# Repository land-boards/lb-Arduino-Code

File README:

These are my arduino files. Some of these files (particularly libraries) were created by others. 

Many of them were created by me based on the work of others.

Use at your own risk. If you brick your part or it melt to a puddle, it's on you not me.

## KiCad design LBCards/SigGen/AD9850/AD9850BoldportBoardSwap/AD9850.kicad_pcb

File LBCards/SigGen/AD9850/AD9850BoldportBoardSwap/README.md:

### AD9850 Signal Generator Boldport Board Swap Version

This is the KiCAD files and Gerber files for the Boldport Board Swap.  It is a driver board for an AD9850 module. It uses an  ATMega328p as the controll chip and includes a display as well as two rotary encoders to support a UI.

It is based on the project:

http://www.vwlowen.co.uk/arduino/AD9850-waveform-generator/AD9850-waveform-generator.htm

Which in turn is based on AD9851 code from Andrew Smallbone - modified for AD9850 http://www.rocketnumbernine.com/2011/10/25/programming-the-ad9851-dds-synthesizer

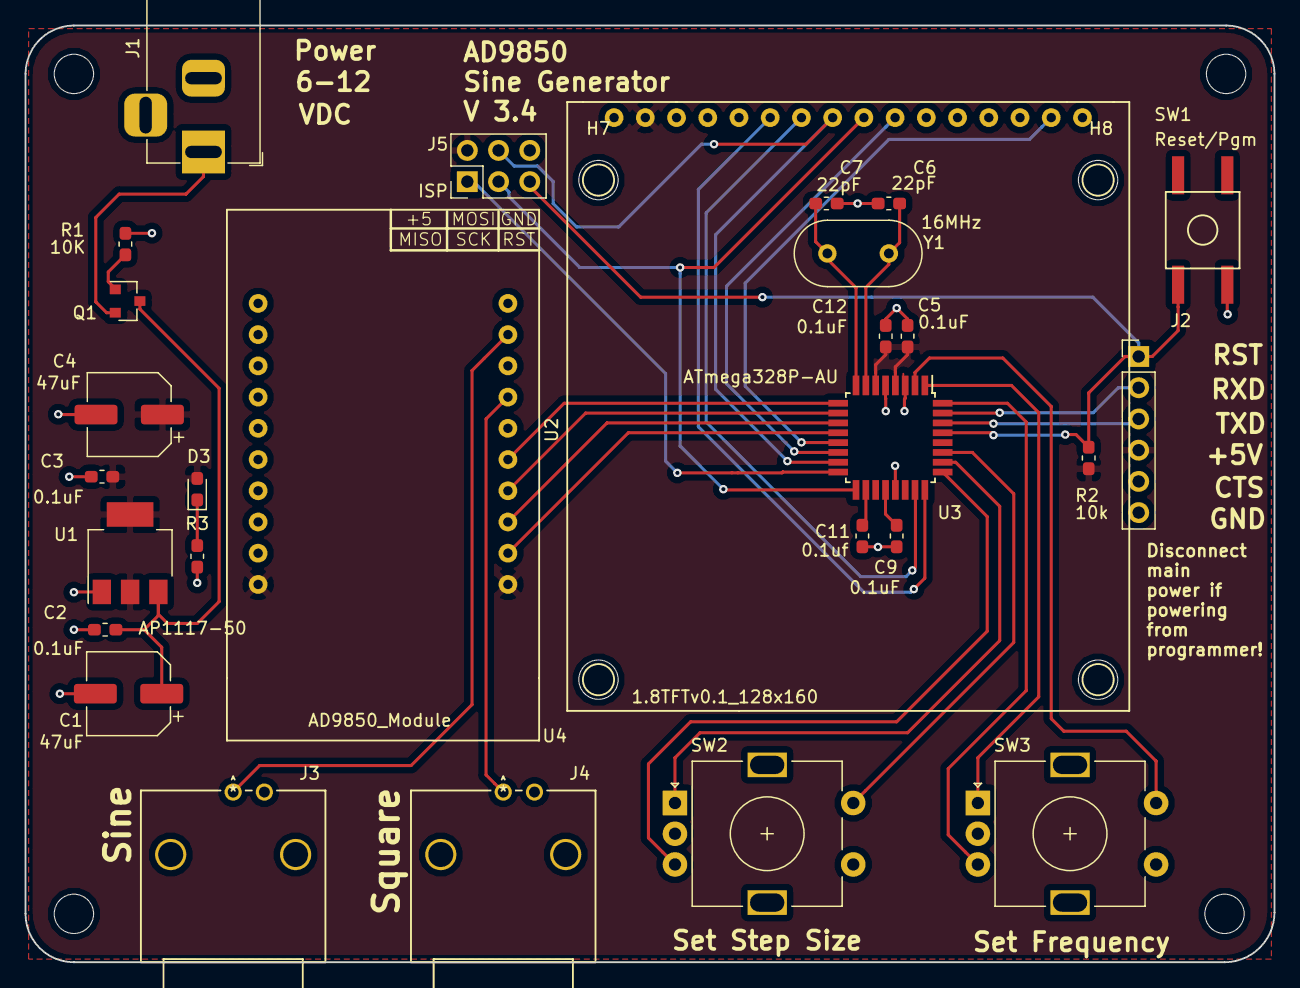
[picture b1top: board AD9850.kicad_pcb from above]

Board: 2 copper layers, 101.6 x 76.2 mm, 36 parts (0 on the bottom side), 32 nets.

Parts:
C1, C4: 47uF; CP_Elec_6.3x7.7
C2, C3, C5, C9, C12: 0.1uF; C_0603_1608Metric_Pad1.05x0.95mm_HandSolder
C6, C7: 22pF; C_0603_1608Metric_Pad1.05x0.95mm_HandSolder
C11: 0.1uf; C_0603_1608Metric_Pad1.05x0.95mm_HandSolder
D3: Power LED; D_0603_1608Metric_Pad1.05x0.95mm_HandSolder
H1, H2, H3, H4, H5, H6, H7, H8: MountingHole; MountingHole_3.2mm_M3
J1: Power In; BarrelJack_Horizontal
J2: PGM Header; PinHeader_1x06_P2.54mm_Vertical
J3: Square Out; 5227161-9
J4: Sine Out; 5227161-9
J5: ISP; PinHeader_2x03_P2.54mm_Vertical
Q1: IRLML9301; SOT-23
R1: 10K; R_0603_1608Metric_Pad1.05x0.95mm_HandSolder
R2: 10k; R_0603_1608Metric_Pad1.05x0.95mm_HandSolder
R3: 330; R_0603_1608Metric_Pad1.05x0.95mm_HandSolder
SW1: Reset/Pgm; SW_MC_SMD_6.0mmx6.4mm
SW2: Set_Step; RotaryEncoder_Alps_EC11E-Switch_Vertical_H20mm
SW3: Set_Freq; RotaryEncoder_Alps_EC11E-Switch_Vertical_H20mm
U1: AP1117-50; SOT-223-3_TabPin2
U2: 1.8TFTv0.1_128x160; 128x160-SPI_w_SD-CARD
U3: ATmega328P-AU; TQFP-32_7x7mm_P0.8mm
U4: AD9850_Module; DS9850_Module
Y1: 16MHz; Resonator-2Pin_W10.0mm_H5.0mm

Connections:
+5V: C3.1, C4.1, C5.1, C12.1, D3.2, J2.4, J5.2, R2.1, U1.2, U2.2, U3.4, U3.6, U4.1, U4.20
+VDC: J1.1, Q1.2
/CS: U2.10, U3.14
/DC: U2.7, U3.23
/DTR: J2.1, J5.5, R2.2, SW1.2, U3.29
/FREQ1: SW3.B, U3.32
/FREQ2: SW3.A, U3.1
/MISO_BLDR: J5.1, U3.16
/MOSI: J5.4, U2.8, U3.15
/RXD: J2.2, U3.31
/SCK: J5.3, U2.9, U3.17
/SET_1Hz_Step: SW2.S2, U3.27
/SET_1kHz_Freq: SW3.S2, U3.2
/STEP1: SW2.B, U3.25
/STEP2: SW2.A, U3.26
/TFT_RST: U2.6, U3.24
/TXD: J2.3, U3.30
GND: C1.2, C2.2, C3.2, C4.2, C5.2, C6.1, C7.1, C9.1, C11.1, C12.2, J1.2, J2.6, J3.2, J4.2, J5.6, R1.2, R3.2, SW1.1, SW2.C, SW2.S1, SW3.C, SW3.S1, U1.1, U2.1, U2.16, U3.3, U3.5, U3.21, U4.6, U4.11
unnamed: C1.1, C2.1, Q1.3, U1.3
unnamed: C6.2, U3.7, Y1.1
unnamed: C7.2, U3.8, Y1.2
unnamed: C9.2, U3.20
unnamed: C11.2, U3.18
unnamed: D3.1, R3.1
unnamed: J3.1, U4.9
unnamed: J4.1, U4.7
unnamed: Q1.1, R1.1
unnamed: U2.15, U3.13
unnamed: U3.9, U4.5
unnamed: U3.10, U4.4
unnamed: U3.11, U4.3
unnamed: U3.12, U4.2

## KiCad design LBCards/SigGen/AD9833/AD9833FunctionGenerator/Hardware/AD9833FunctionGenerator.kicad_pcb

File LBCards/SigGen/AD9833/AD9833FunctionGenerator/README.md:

# DDS Function Generator
## Specification
- Produces sine, square, triange output
- Output waveform resolution of 0.1 Hz
- Frequency range: 1Hz - 100KHz
- Selectable ranges: 0-1KHz, 0-10KHz, 0-100KHz
- Frequency sweep mode with lower/upper range and speed control.
- Output amplitude up to 10 V peak-to-peak (+20dBv)
- DC offset voltage adjustable between -10V to +10V
- Output impedance of 600 Ω.

---

## Improved signal integrity at 100KHz
This is the square wave signal with +20dBv gain @ 10KHz

This is the same signal @ 100KHz. You can see the TL071 opamp (3MHz Unity GBP) is unable to amplify the huge number of odd-integer harmonics of the waveform. This has an undesirable bandpass filter effect on the signal.

The LM7171 opamp (200MHz Unity GBP) is able to maintain the square wave harmonics for +20dBv @ 100KHz.  

---

## Schematic

[Schematic](https://github.com/cracked-machine/AD9833FunctionGenerator/blob/master/docs/Schematic/AD9833FunctionGenerator.pdf)

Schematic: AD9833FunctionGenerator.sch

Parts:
A1: Arduino_Nano_v3.x; Arduino_Nano
C1: 220nF; C_0805_2012Metric_Pad1.15x1.40mm_HandSolder
C2: 100nF; C_0805_2012Metric_Pad1.15x1.40mm_HandSolder
CPWRBP1, CPWRBP2: 100nF; C_0805_2012Metric_Pad1.15x1.40mm_HandSolder
C_POTBP1: 100nF; C_0805_2012Metric_Pad1.15x1.40mm_HandSolder
J_AD9833: Conn_01x07; PinSocket_1x07_P2.54mm_Vertical
J_OUT1: Conn_01x02; PinSocket_1x02_P2.54mm_Vertical
J_PWR1: Conn_02x05_Odd_Even; PinHeader_2x05_P2.54mm_Vertical
ROFF1, ROFF2: 1K; R_0805_2012Metric_Pad1.15x1.40mm_HandSolder
RV_FREQ1: B10K; PTH901; MouserPartNo 652-PTH901-030S-103B
RV_TIME1: R_POT_Dual_Separate; PTH901
R_PHASE1: 100R; R_0805_2012Metric_Pad1.15x1.40mm_HandSolder
R_VEL1: 100R; R_0805_2012Metric_Pad1.15x1.40mm_HandSolder
SW_PWR1: SW_DPDT_x2; ALPS_SPUN191600
U1: LM7805_TO220; TO-220-3_Vertical; MouserPartNo 926-LM7805CT/NOPB
U_POT1: MCP42050; SOIC-14_3.9x8.7mm_P1.27mm; MouserPartNo 579-MCP42050-I/SL

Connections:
/5V: A1.30, C2.1, C_POTBP1.1, J_AD9833.2, ROFF1.2, RV_FREQ1.3, RV_FREQ1.6, RV_TIME1.1, RV_TIME1.4, U1.3, U_POT1.11 (~RS), U_POT1.12 (~SHDN), U_POT1.14 (VDD); also elsewhere on the board
/+12V: C1.1, CPWRBP1.1, SW_PWR1.1, U1.1; also elsewhere on the board
/-12V: CPWRBP2.2, SW_PWR1.4; also elsewhere on the board
/AREF: A1.17, A1.18
/DDS_CS: A1.13, J_AD9833.6
/DDS_REDUX: U_POT1.9 (PW0); also elsewhere on the board
/DDS_SIG: J_AD9833.7, U_POT1.8 (PA0)
/FREQHI: A1.19, RV_FREQ1.5
/FREQLO: A1.20, RV_FREQ1.2
/GND: A1.4, A1.29, C1.2, C2.2, CPWRBP1.2, CPWRBP2.1, C_POTBP1.2, J_AD9833.3, J_OUT1.2, J_PWR1.4, J_PWR1.6, J_PWR1.8, ROFF2.2, RV_FREQ1.1, RV_FREQ1.4, R_PHASE1.1, R_VEL1.1, U1.2, U_POT1.4 (VSS), U_POT1.10 (PB0); also elsewhere on the board
/MODEBTN: A1.6; also elsewhere on the board
/MOSI: A1.14, J_AD9833.4, U_POT1.3 (SI)
/OFFSETADJUST: U_POT1.6 (PW1); also elsewhere on the board
/OutputSection/SIGOUT: J_OUT1.1; also elsewhere on the board
/PHASE1: A1.22, RV_TIME1.5
/POT_CS: A1.12, U_POT1.1 (~CS)
/RANGEBTN: A1.8; also elsewhere on the board
/SCK: A1.16, J_AD9833.5, U_POT1.2 (SCK)
/SCL: A1.24; also elsewhere on the board
/SDA: A1.23; also elsewhere on the board
/VEL1: A1.25, RV_TIME1.2
/WAVEBTN: A1.5; also elsewhere on the board
unnamed: J_PWR1.2, SW_PWR1.2
unnamed: J_PWR1.10, SW_PWR1.5
unnamed: ROFF1.1, U_POT1.7 (PA1)
unnamed: ROFF2.1, U_POT1.5 (PB1)
unnamed: RV_TIME1.3, R_VEL1.2
unnamed: RV_TIME1.6, R_PHASE1.2

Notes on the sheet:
REF VCC GND DAT CLK FNC OUT
DDS Signal Generation
Output Amplifier Section
Power Supply Section
Peripheral Controls section
Signal Compensation
Micocontroller

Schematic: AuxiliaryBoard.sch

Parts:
J_AUX2MAIN2: Conn_02x05_Odd_Even; PinHeader_2x05_P2.54mm_Vertical
J_MAIN2AUX1: Conn_02x05_Odd_Even; PinHeader_2x05_P2.54mm_Vertical
J_OLEDCONNECTOR1: Conn_01x04; PinSocket_1x04_P2.54mm_Vertical
R_FUNC1: 1K; R_0805_2012Metric_Pad1.15x1.40mm_HandSolder
R_MODE1: 1K; R_0805_2012Metric_Pad1.15x1.40mm_HandSolder
R_RANGE1: 1K; R_0805_2012Metric_Pad1.15x1.40mm_HandSolder
SW_FUNC1: SW_SPST; SW_PUSH_6mm; MouserPartNo 688-SKHHDJA010
SW_MODE1: SW_SPST; SW_PUSH_6mm; MouserPartNo 688-SKHHDJA010
SW_RANGE1: SW_SPST; SW_PUSH_6mm; MouserPartNo 688-SKHHDJA010

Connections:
/5V: J_MAIN2AUX1.1; also elsewhere on the board
/AuxiliaryBoard/5V_AUX: J_AUX2MAIN2.1, J_OLEDCONNECTOR1.1, SW_FUNC1.1, SW_MODE1.1, SW_RANGE1.1
/AuxiliaryBoard/GND_AUX: J_AUX2MAIN2.3, J_OLEDCONNECTOR1.2, R_FUNC1.1, R_MODE1.1, R_RANGE1.1
/AuxiliaryBoard/MODEBTN_AUX: J_AUX2MAIN2.7, R_MODE1.2, SW_MODE1.2
/AuxiliaryBoard/RANGEBTN_AUX: J_AUX2MAIN2.5, R_RANGE1.2, SW_RANGE1.2
/AuxiliaryBoard/SCL_AUX: J_AUX2MAIN2.8, J_OLEDCONNECTOR1.3
/AuxiliaryBoard/SDA_AUX: J_AUX2MAIN2.10, J_OLEDCONNECTOR1.4
/AuxiliaryBoard/WAVEBTN_AUX: J_AUX2MAIN2.9, R_FUNC1.2, SW_FUNC1.2
/GND: J_MAIN2AUX1.3; also elsewhere on the board
/MODEBTN: J_MAIN2AUX1.7; also elsewhere on the board
/RANGEBTN: J_MAIN2AUX1.5; also elsewhere on the board
/SCL: J_MAIN2AUX1.8; also elsewhere on the board
/SDA: J_MAIN2AUX1.10; also elsewhere on the board
/WAVEBTN: J_MAIN2AUX1.9; also elsewhere on the board

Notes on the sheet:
Input Connector
Output Connector
Display Connector

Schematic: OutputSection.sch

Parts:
CF1, CF2: 2pF; C_0805_2012Metric_Pad1.15x1.40mm_HandSolder
C_BUFFBP1, C_BUFFBP4: 2.2uF; C_0805_2012Metric_Pad1.15x1.40mm_HandSolder
C_BUFFBP2, C_BUFFBP3: 100nF; C_0805_2012Metric_Pad1.15x1.40mm_HandSolder
C_GAIN1: 470pF; C_0805_2012Metric_Pad1.15x1.40mm_HandSolder
C_MIXBP1, C_MIXBP4: 2.2uF; C_0805_2012Metric_Pad1.15x1.40mm_HandSolder
C_MIXBP2, C_MIXBP3: 100nF; C_0805_2012Metric_Pad1.15x1.40mm_HandSolder
RF1: 1k; R_0805_2012Metric_Pad1.15x1.40mm_HandSolder
RF2: 8K2; R_0805_2012Metric_Pad1.15x1.40mm_HandSolder
RG1: 1k; R_0805_2012Metric_Pad1.15x1.40mm_HandSolder
RV_AMP1: B10K; PTH901; MouserPartNo 652-PTH901-030S-103B
RV_LOWOFF1: 100K; Potentiometer_Piher_PT-6-V_Vertical; MouserPartNo 652-3296Y-1-104LF
RV_UPOFF1: 100K; Potentiometer_Piher_PT-6-V_Vertical; MouserPartNo 652-3296Y-1-104LF
R_HIOFF1: 1K; R_0805_2012Metric_Pad1.15x1.40mm_HandSolder
R_ISO1: 600R 1%; R_0805_2012Metric_Pad1.15x1.40mm_HandSolder
R_LOFF1: 1K; R_0805_2012Metric_Pad1.15x1.40mm_HandSolder
R_MIX1, R_MIX2, R_MIX3: 1K; R_0805_2012Metric_Pad1.15x1.40mm_HandSolder
TP_OFF1: TestPoint; TestPoint_Pad_D2.0mm
U_BUFF1: LM7171; SOIC-8_3.9x4.9mm_P1.27mm
U_MIX1: LM7171; SOIC-8_3.9x4.9mm_P1.27mm

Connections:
/+12V: C_BUFFBP1.1, C_BUFFBP2.1, C_MIXBP1.1, C_MIXBP2.1, R_HIOFF1.1, U_BUFF1.7, U_MIX1.7; also elsewhere on the board
/-12V: C_BUFFBP3.1, C_BUFFBP4.1, C_MIXBP3.1, C_MIXBP4.1, R_LOFF1.1, U_BUFF1.4, U_MIX1.4; also elsewhere on the board
/DDS_REDUX: U_BUFF1.3; also elsewhere on the board
/GND: C_BUFFBP1.2, C_BUFFBP2.2, C_BUFFBP3.2, C_BUFFBP4.2, C_GAIN1.2, C_MIXBP1.2, C_MIXBP2.2, C_MIXBP3.2, C_MIXBP4.2, RG1.1, U_MIX1.3; also elsewhere on the board
/OFFSETADJUST: R_MIX3.1; also elsewhere on the board
/OutputSection/SIGOUT: R_ISO1.1; also elsewhere on the board
unnamed: CF1.1, RF1.1, R_MIX1.1, U_BUFF1.6
unnamed: CF1.2, RF1.2, RG1.2, U_BUFF1.2
unnamed: CF2.1, RF2.1, R_ISO1.2, U_MIX1.6
unnamed: CF2.2, C_GAIN1.1, RF2.2, RV_AMP1.4, U_MIX1.2
unnamed: RV_AMP1.1, RV_UPOFF1.1, RV_UPOFF1.2
unnamed: RV_AMP1.2, R_MIX2.1, TP_OFF1.1
unnamed: RV_AMP1.3, RV_LOWOFF1.1, RV_LOWOFF1.2
unnamed: RV_AMP1.5, RV_AMP1.6, R_MIX1.2, R_MIX2.2, R_MIX3.2
unnamed: RV_LOWOFF1.3, R_LOFF1.2
unnamed: RV_UPOFF1.3, R_HIOFF1.2

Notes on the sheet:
User Offset
MCU Offset
User Gain

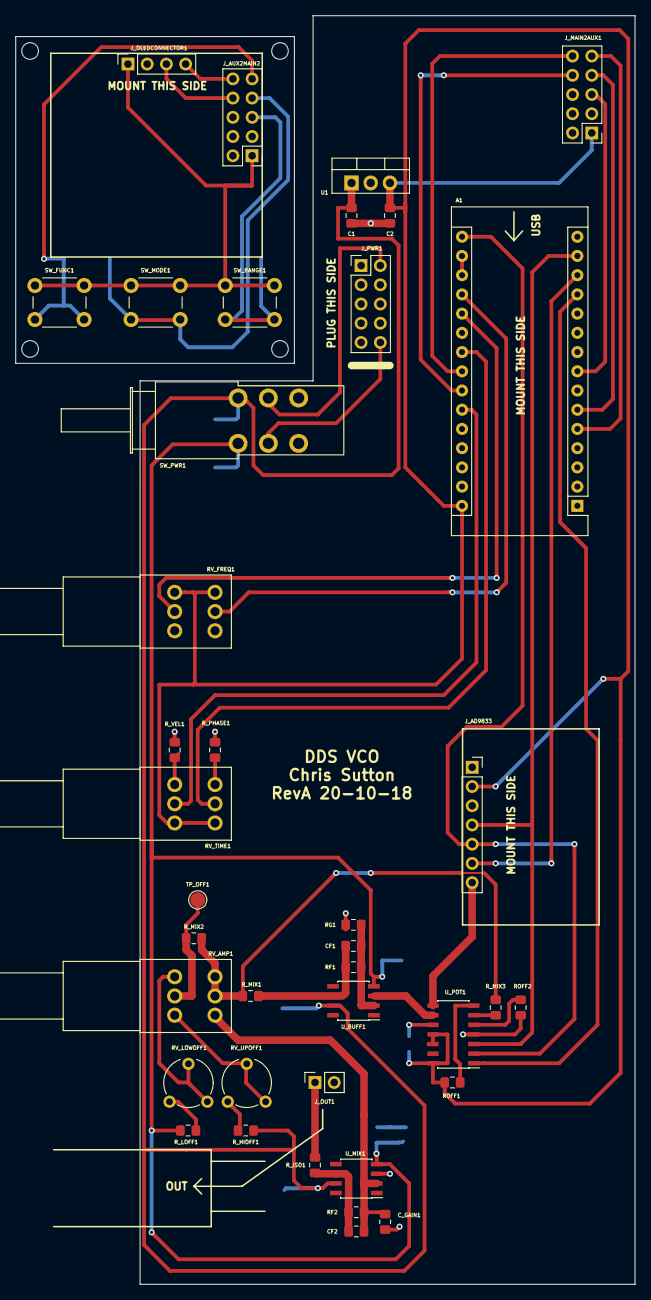
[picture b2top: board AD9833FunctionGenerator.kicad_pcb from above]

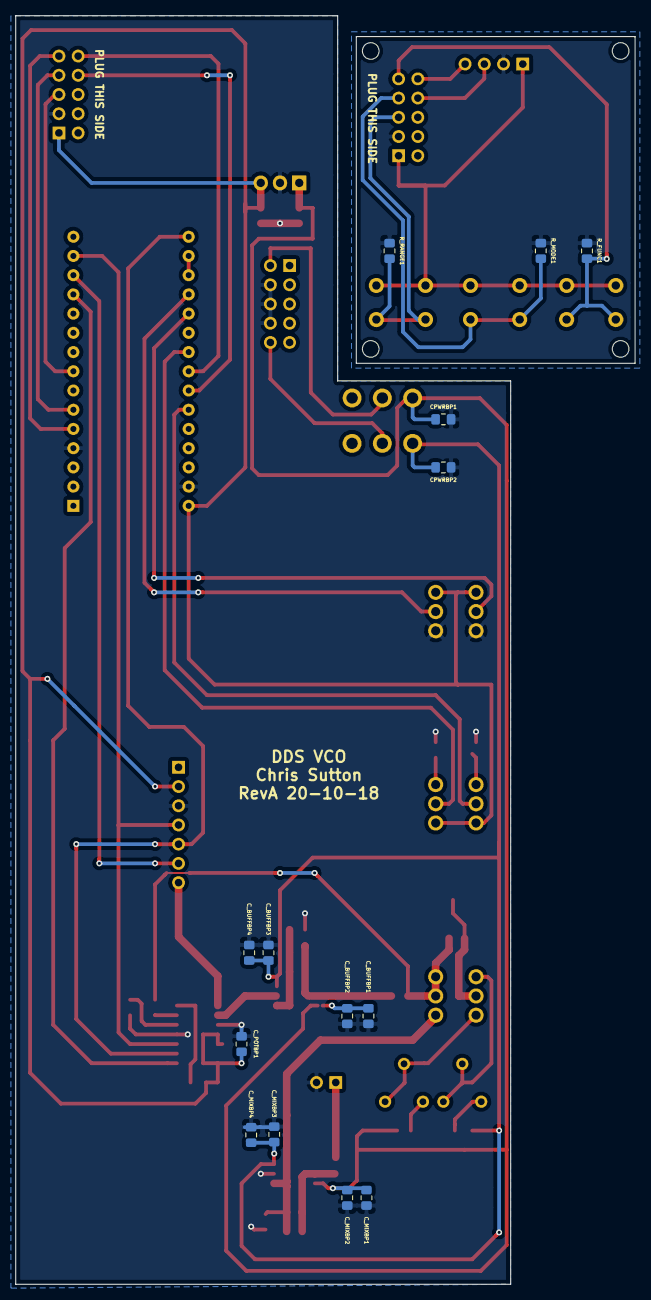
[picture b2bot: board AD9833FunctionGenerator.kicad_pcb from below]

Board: 2 copper layers, 81.8 x 167.6 mm, 53 parts (14 on the bottom side), 45 nets.

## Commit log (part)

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2022-03-17 ODAS Card tester and library updates
2022-03-18 `Test Code
2022-03-19 Added I2C detection code
2022-03-20 Auto detect card type code
2022-03-21 Separate out card detection
2022-03-21 Fixed pinMode function
    I2CIO-8X card internal and external loopback tests working
2022-03-21 I2CIO-8X card test running
2022-03-21 I2CIO-8X Bounce LEDs working
2022-03-21 board test code
2022-03-22 Add internal test code
    Use GPIO Pullup register for testing
2022-03-23 Working code
2022-04-01 I2C-RPT-01 card test working
2022-04-03 Worked I2C-RPT-08 card driver and tests
2022-04-06 STM I2C speed options
2022-04-07 Lot of library updates
    Add STM32 architectures
2022-04-07 Update Si5351 library
2022-05-04 TinyPS2
2022-05-04 TinyPS2 Test routines
2022-05-04 Archive others
2022-05-04 Add delay between chars
2022-05-04 Working on kbd to serial
2022-05-05 Got TinyPS2 working under Arduino environment
2022-05-05 Added comments for source of sources
2022-05-21 Arduino In a Box code
2022-05-21 Fix folder name
2022-05-21 Clean up docs
2022-05-22 Demo code
2022-05-22 Menu Demo code
2022-05-24 SWLEDX8 example code added to Arduino In a Box example
2022-05-30 some library stuff
2022-06-05 SD Card Driver files
2022-06-06 Shuffle files
2022-06-07 test code working
2022-06-07 Menu system MVP
2022-06-07 Update library
2022-06-08 SD card Info working
2022-06-09 Menu working, dir working
2022-06-10 Adding directory
2022-06-11 LEDs in XIAO RP2040 card
2022-06-13 Land Boards Seven Segment demo code
2022-06-14 QT Py code
2022-06-19 Copy PROTO16 file to I2CIO16 card
2022-06-19 Update file headers
2022-06-23 GPS Frequency Standard Code
2022-06-25 Generate GPS freq values as bytestrings
2022-06-26 shuffle files into GPS folver
2022-07-08 Update libraries
2022-07-26 MAX7219X4 card
2022-07-29 MAX7219X4 driver code
2022-08-15 TinyPS2 Rev 4 working
2022-09-03 ESP32-VGA software
2022-09-20 USB to SERIAL CONVERTER
2022-10-04 MOZZI
2022-10-06 More Synths
2022-10-11 esp32 synth
2022-10-14 VCO code
2022-11-08 ER CODE
2022-11-10 SHUFFLE SYNTH FILES
2022-11-20 MOZZI and HAGIWO
2022-11-20 HAGIWO FM VCO
2022-11-20 HAGIWO BUILDS
2022-11-22 UPDATE LIBS, BOARDS
2022-11-25 TESTING VCO CODE ON ER-MOZZI CARD
2022-11-28 ER-MIDI-CV4 card code
2022-11-28 Test code
2022-11-28 Working basically
2022-11-29 Added many comments
2022-11-29 fixed high notes count
2022-12-03 synths
2022-12-03 TRIPLE VCO OUT
2022-12-06 Make note CV persist until next note pressed
2022-12-09 Fix overflow timer hangs
    micros() - Overflows at 70 mins
2022-12-10 Alternate random CV Generator
2022-12-10 First cut of random CV code
2022-12-10 Make RV1 = Note speeds, RV2 = Gate percentage time
2022-12-13 Made rate pot logarithmic
2022-12-22 NeoPixels for the Eurorack build
2022-12-22 Improve NeoPixel modes, add comments
2022-12-23 STM32
2022-12-27 STIX (DIY Branches) code
2022-12-28 update STIX
2023-01-04 GATE SEQUENCER
2023-01-07 FFT library
2023-01-07 Encoder test code
2023-01-07 Use Arduino direct port manipulation
2023-01-07 ER-SCOPE hardware test
2023-01-08 ER-SCOPE working code
2023-01-20 ER-MOZZI-DRUMS

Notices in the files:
parts and their libraries:
Copyright 2016 Accelerated Designs. All rights reserved.
